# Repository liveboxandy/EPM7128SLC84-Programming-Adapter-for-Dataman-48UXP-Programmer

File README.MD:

# EPM7128SLC84-Programming-Adapter-for-Dataman-48UXP-Programmer

This adapter allows a Dataman UXP48 parallel programmer to program Altera EPM7128SLC84 devices that have been JTAG locked. 

The pinout has been taken from the Dataman documentation and I see no reason why it shouldn't work on any EPM7128 PLCC84 devices as they all use the same adapter SDP-7128-84 according to the documentation. 

Note that the Dataman XP and XP48 will only do 5V devices while the 48LV and 48UXP will do 3V3 devices as well

Note that the pinout is unique to the EPM7128 Series. The EPM7032, EPM7064 and EPM7160 all have their own uniquely wired adapters.

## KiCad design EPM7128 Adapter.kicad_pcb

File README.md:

# EPM7128SLC84-Programming-Adapter-for-Dataman-48UXP-Programmer

This adapter allows a Dataman UXP48 parallel programmer to program Altera EPM7128SLC84 devices that have been JTAG locked. 

The pinout has been taken from the Dataman documentation and I see no reason why it shouldn't work on any EPM7128 PLCC84 devices as they all use the same adapter SDP-7128-84 according to the documentation. 

Note that the Dataman XP and XP48 will only do 5V devices while the 48LV and 48UXP will do 3V3 devices as well

Note that the pinout is unique to the EPM7128 Series. The EPM7032, EPM7064 and EPM7160 all have their own uniquely wired adapters.

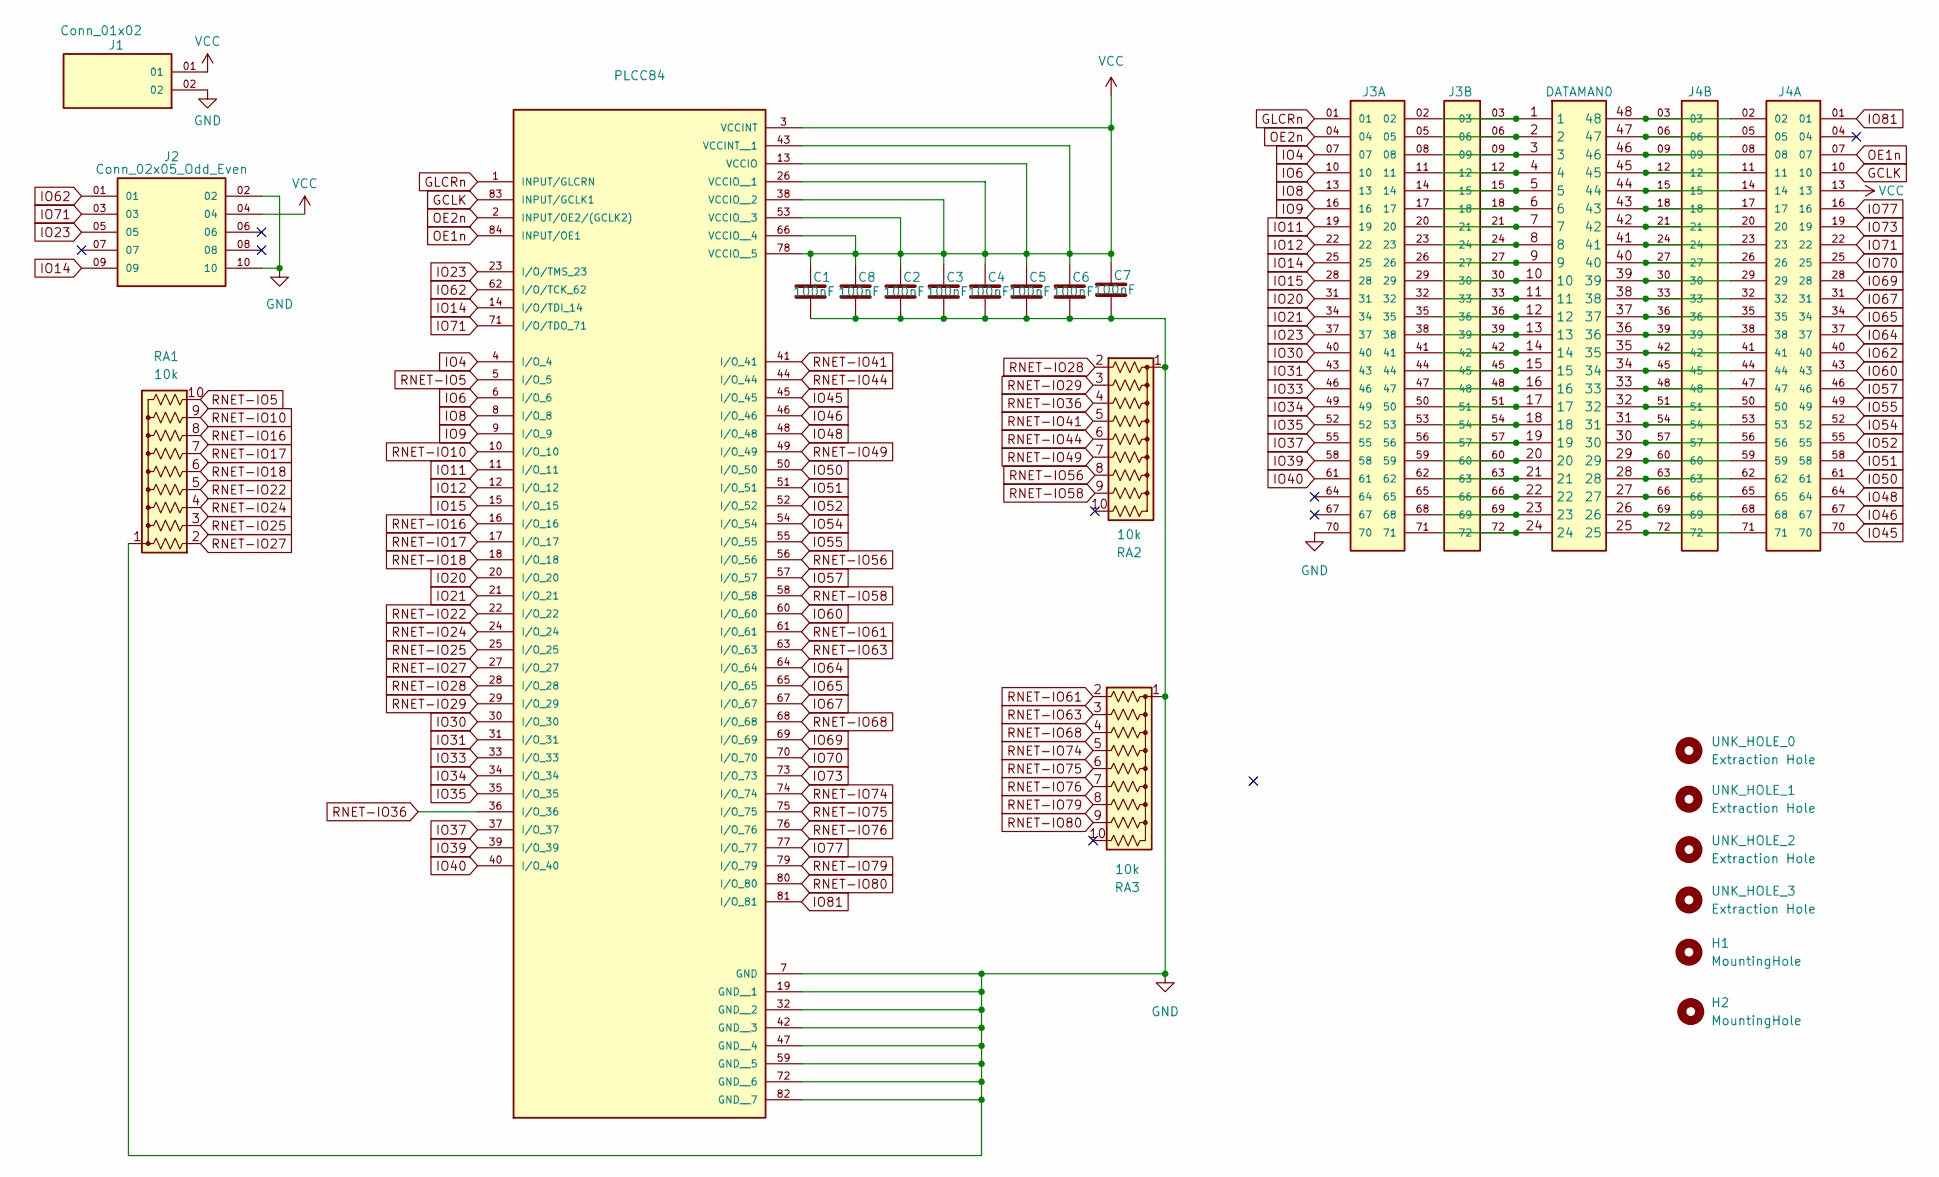
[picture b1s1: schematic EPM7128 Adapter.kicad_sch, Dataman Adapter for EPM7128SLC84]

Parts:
C1, C2, C3, C4, C5, C6, C7, C8: 100nF; C1206
DATAMAN0: Pin-Pin Headers 1x24; DIL48
H1, H2: MountingHole; MountingHole_2.7mm_M2.5
J1: Conn_01x02; SAMTEC_TSW-102-07-G-S; PARTREV R
J2: Conn_02x05_Odd_Even; SAMTEC_TSW-105-07-L-D; PARTREV R; DigiKey_Part_Number SAM1030-05-ND
J3, J4: TSW-124-08-T-T; SAMTEC_TSW-124-08-T-T; PARTREV R
PLCC84: PLCC84AT
RA1, RA2, RA3: 10k; 4610M101103LF
UNK_HOLE_0, UNK_HOLE_1, UNK_HOLE_2, UNK_HOLE_3: Extraction Hole; MountingHole_2.7mm_M2.5

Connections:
GCLK: J4.10, PLCC84.83 (INPUT/GCLK1)
GLCRn: J3.01, PLCC84.1 (INPUT/GLCRN)
GND: C1.2, C2.2, C3.2, C4.2, C5.2, C6.2, C7.2, C8.2, J1.02, J2.02, J2.10, J3.70, PLCC84.7 (GND), PLCC84.19 (GND__1), PLCC84.32 (GND__2), PLCC84.42 (GND__3), PLCC84.47 (GND__4), PLCC84.59 (GND__5), PLCC84.72 (GND__6), PLCC84.82 (GND__7), RA1.1 (common), RA2.1 (common), RA3.1 (common)
IO4: J3.07, PLCC84.4 (I/O_4)
IO6: J3.10, PLCC84.6 (I/O_6)
IO8: J3.13, PLCC84.8 (I/O_8)
IO9: J3.16, PLCC84.9 (I/O_9)
IO11: J3.19, PLCC84.11 (I/O_11)
IO12: J3.22, PLCC84.12 (I/O_12)
IO14: J2.09, J3.25, PLCC84.14 (I/O/TDI_14)
IO15: J3.28, PLCC84.15 (I/O_15)
IO20: J3.31, PLCC84.20 (I/O_20)
IO21: J3.34, PLCC84.21 (I/O_21)
IO23: J2.05, J3.37, PLCC84.23 (I/O/TMS_23)
IO30: J3.40, PLCC84.30 (I/O_30)
IO31: J3.43, PLCC84.31 (I/O_31)
IO33: J3.46, PLCC84.33 (I/O_33)
IO34: J3.49, PLCC84.34 (I/O_34)
IO35: J3.52, PLCC84.35 (I/O_35)
IO37: J3.55, PLCC84.37 (I/O_37)
IO39: J3.58, PLCC84.39 (I/O_39)
IO40: J3.61, PLCC84.40 (I/O_40)
IO45: J4.70, PLCC84.45 (I/O_45)
IO46: J4.67, PLCC84.46 (I/O_46)
IO48: J4.64, PLCC84.48 (I/O_48)
IO50: J4.61, PLCC84.50 (I/O_50)
IO51: J4.58, PLCC84.51 (I/O_51)
IO52: J4.55, PLCC84.52 (I/O_52)
IO54: J4.52, PLCC84.54 (I/O_54)
IO55: J4.49, PLCC84.55 (I/O_55)
IO57: J4.46, PLCC84.57 (I/O_57)
IO60: J4.43, PLCC84.60 (I/O_60)
IO62: J2.01, J4.40, PLCC84.62 (I/O/TCK_62)
IO64: J4.37, PLCC84.64 (I/O_64)
IO65: J4.34, PLCC84.65 (I/O_65)
IO67: J4.31, PLCC84.67 (I/O_67)
IO69: J4.28, PLCC84.69 (I/O_69)
IO70: J4.25, PLCC84.70 (I/O_70)
IO71: J2.03, J4.22, PLCC84.71 (I/O/TDO_71)
IO73: J4.19, PLCC84.73 (I/O_73)
IO77: J4.16, PLCC84.77 (I/O_77)
IO81: J4.01, PLCC84.81 (I/O_81)
unnamed: DATAMAN0.1, J3.02, J3.03
unnamed: DATAMAN0.2, J3.05, J3.06
unnamed: DATAMAN0.3, J3.08, J3.09
unnamed: DATAMAN0.4, J3.11, J3.12
unnamed: DATAMAN0.5, J3.14, J3.15
unnamed: DATAMAN0.6, J3.17, J3.18
unnamed: DATAMAN0.7, J3.20, J3.21
unnamed: DATAMAN0.8, J3.23, J3.24
unnamed: DATAMAN0.9, J3.26, J3.27
unnamed: DATAMAN0.10, J3.29, J3.30
unnamed: DATAMAN0.11, J3.32, J3.33
unnamed: DATAMAN0.12, J3.35, J3.36
unnamed: DATAMAN0.13, J3.38, J3.39
unnamed: DATAMAN0.14, J3.41, J3.42
unnamed: DATAMAN0.15, J3.44, J3.45
unnamed: DATAMAN0.16, J3.47, J3.48
unnamed: DATAMAN0.17, J3.50, J3.51
unnamed: DATAMAN0.18, J3.53, J3.54
unnamed: DATAMAN0.19, J3.56, J3.57
unnamed: DATAMAN0.20, J3.59, J3.60
unnamed: DATAMAN0.21, J3.62, J3.63
unnamed: DATAMAN0.22, J3.65, J3.66
unnamed: DATAMAN0.23, J3.68, J3.69
unnamed: DATAMAN0.24, J3.71, J3.72
unnamed: DATAMAN0.25, J4.71, J4.72
unnamed: DATAMAN0.26, J4.68, J4.69
unnamed: DATAMAN0.27, J4.65, J4.66
unnamed: DATAMAN0.28, J4.62, J4.63
unnamed: DATAMAN0.29, J4.59, J4.60
unnamed: DATAMAN0.30, J4.56, J4.57
unnamed: DATAMAN0.31, J4.53, J4.54
unnamed: DATAMAN0.32, J4.50, J4.51
unnamed: DATAMAN0.33, J4.47, J4.48
unnamed: DATAMAN0.34, J4.44, J4.45
unnamed: DATAMAN0.35, J4.41, J4.42
unnamed: DATAMAN0.36, J4.38, J4.39
unnamed: DATAMAN0.37, J4.35, J4.36
unnamed: DATAMAN0.38, J4.32, J4.33
unnamed: DATAMAN0.39, J4.29, J4.30
unnamed: DATAMAN0.40, J4.26, J4.27
unnamed: DATAMAN0.41, J4.23, J4.24
unnamed: DATAMAN0.42, J4.20, J4.21
unnamed: DATAMAN0.43, J4.17, J4.18
unnamed: DATAMAN0.44, J4.14, J4.15
unnamed: DATAMAN0.45, J4.11, J4.12
unnamed: DATAMAN0.46, J4.08, J4.09
unnamed: DATAMAN0.47, J4.05, J4.06
unnamed: DATAMAN0.48, J4.02, J4.03
OE1n: J4.07, PLCC84.84 (INPUT/OE1)
OE2n: J3.04, PLCC84.2 (INPUT/OE2/(GCLK2))
RNET-IO5: PLCC84.5 (I/O_5), RA1.10 (R9)
RNET-IO10: PLCC84.10 (I/O_10), RA1.9 (R8)
RNET-IO16: PLCC84.16 (I/O_16), RA1.8 (R7)
RNET-IO17: PLCC84.17 (I/O_17), RA1.7 (R6)
RNET-IO18: PLCC84.18 (I/O_18), RA1.6 (R5)
RNET-IO22: PLCC84.22 (I/O_22), RA1.5 (R4)
RNET-IO24: PLCC84.24 (I/O_24), RA1.4 (R3)
RNET-IO25: PLCC84.25 (I/O_25), RA1.3 (R2)
RNET-IO27: PLCC84.27 (I/O_27), RA1.2 (R1)
RNET-IO28: PLCC84.28 (I/O_28), RA2.2 (R1)
RNET-IO29: PLCC84.29 (I/O_29), RA2.3 (R2)
RNET-IO36: PLCC84.36 (I/O_36), RA2.4 (R3)
RNET-IO41: PLCC84.41 (I/O_41), RA2.5 (R4)
RNET-IO44: PLCC84.44 (I/O_44), RA2.6 (R5)
RNET-IO49: PLCC84.49 (I/O_49), RA2.7 (R6)
RNET-IO56: PLCC84.56 (I/O_56), RA2.8 (R7)
RNET-IO58: PLCC84.58 (I/O_58), RA2.9 (R8)
RNET-IO61: PLCC84.61 (I/O_61), RA3.2 (R1)
RNET-IO63: PLCC84.63 (I/O_63), RA3.3 (R2)
RNET-IO68: PLCC84.68 (I/O_68), RA3.4 (R3)
RNET-IO74: PLCC84.74 (I/O_74), RA3.5 (R4)
RNET-IO75: PLCC84.75 (I/O_75), RA3.6 (R5)
RNET-IO76: PLCC84.76 (I/O_76), RA3.7 (R6)
RNET-IO79: PLCC84.79 (I/O_79), RA3.8 (R7)
RNET-IO80: PLCC84.80 (I/O_80), RA3.9 (R8)
VCC: C1.1, C2.1, C3.1, C4.1, C5.1, C6.1, C7.1, C8.1, J1.01, J2.04, J4.13, PLCC84.3 (VCCINT), PLCC84.13 (VCCIO), PLCC84.26 (VCCIO__1), PLCC84.38 (VCCIO__2), PLCC84.43 (VCCINT__1), PLCC84.53 (VCCIO__3), PLCC84.66 (VCCIO__4), PLCC84.78 (VCCIO__5)

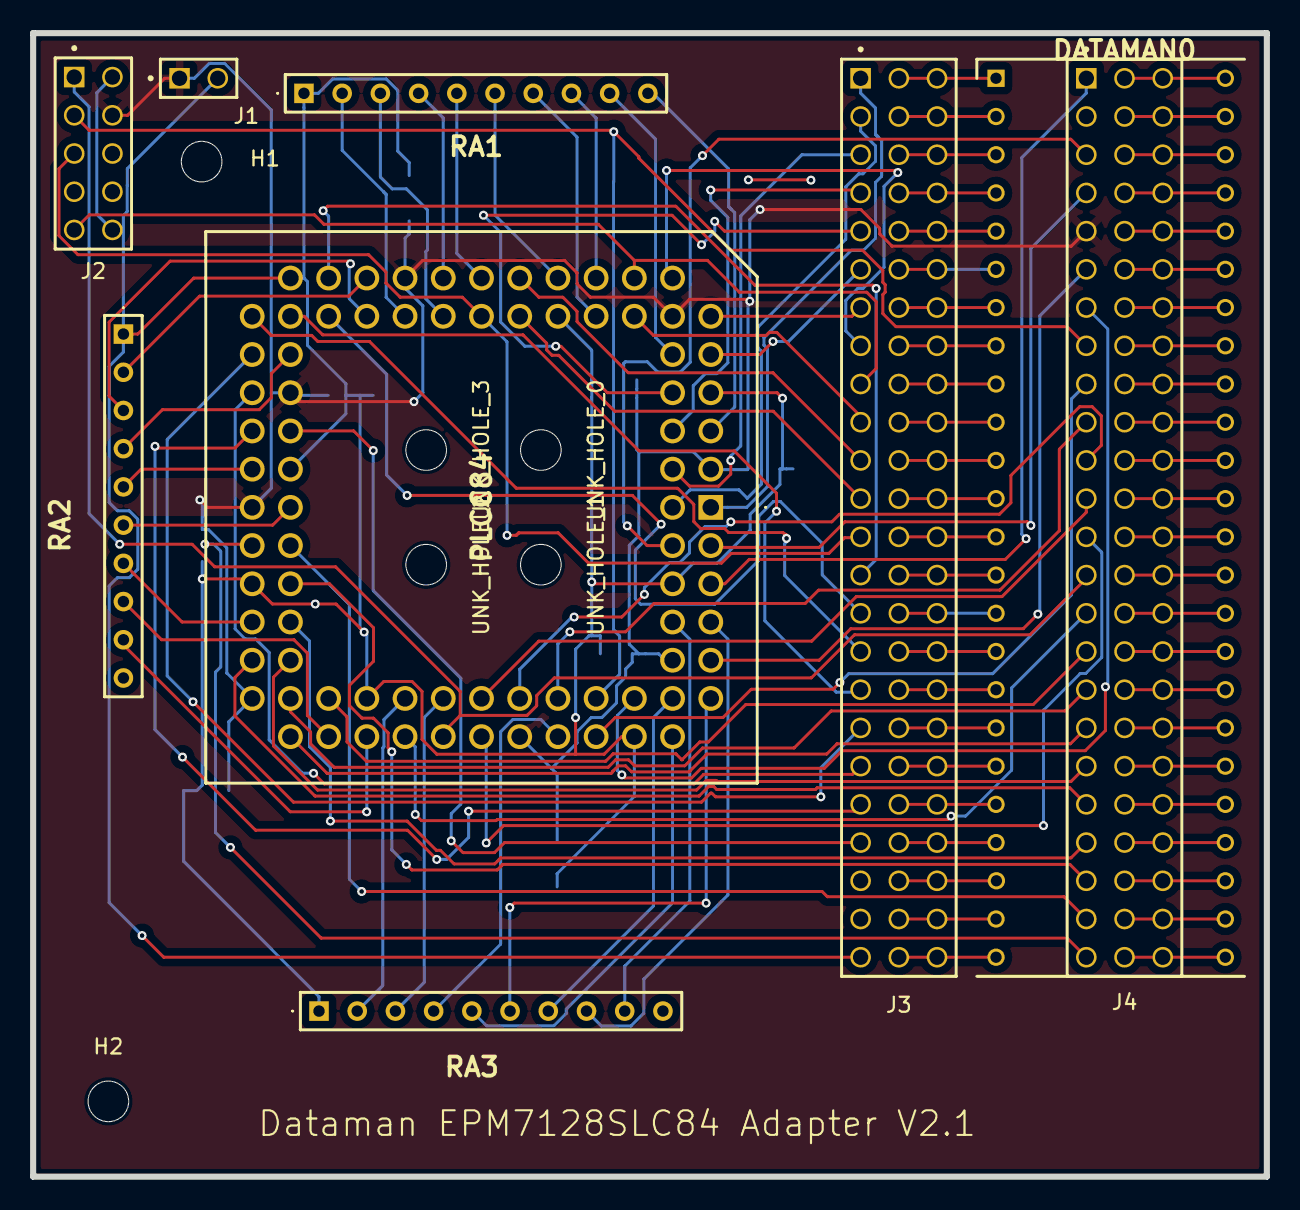
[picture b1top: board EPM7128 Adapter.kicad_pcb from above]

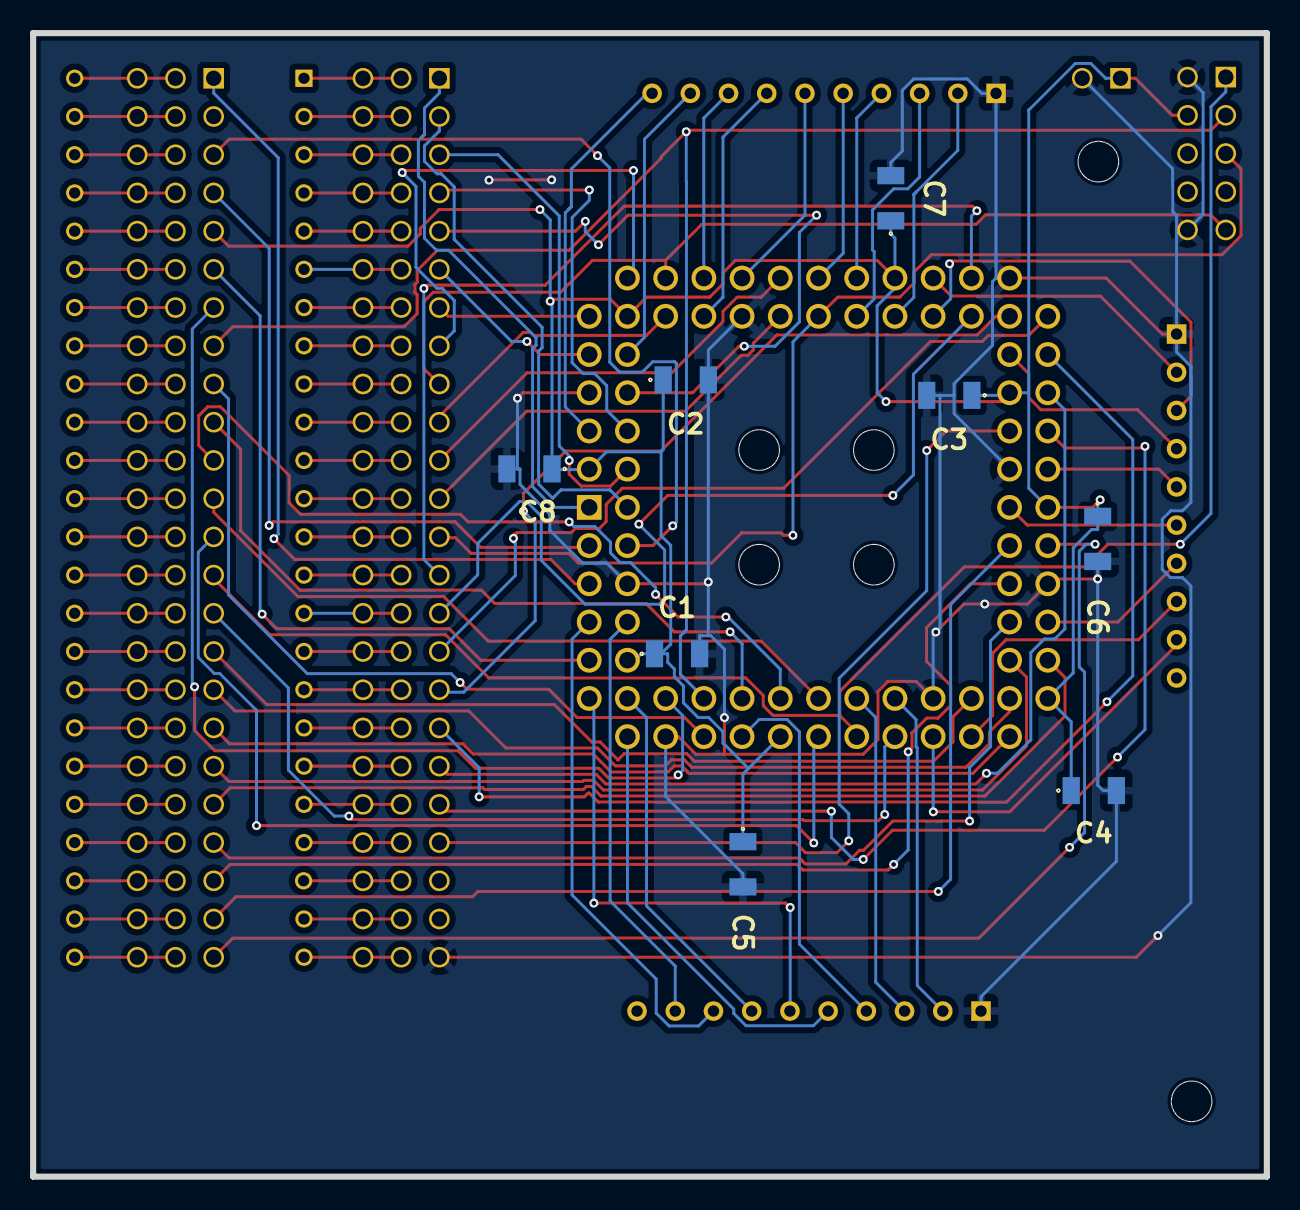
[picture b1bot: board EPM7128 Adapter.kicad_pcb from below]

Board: 2 copper layers, 82.0 x 76.0 mm, 23 parts (8 on the bottom side), 118 nets.

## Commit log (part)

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2026-03-24 Enhance README with adapter details and compatibility
    Added detailed description of the EPM7128SLC84 programming adapter and its compatibility.
2026-03-24 Initial upload of files
2026-04-27 Add files via upload
    Correct issue with lack of Gnd connection to JTAG, RNETs and PLCC Socket.
2026-04-27 Add files via upload
    Update to correct issue with no Gnd connections to PLCC, RNETs and JTAG
